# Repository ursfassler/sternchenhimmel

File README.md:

# Sternchenhimmel #

A small starry sky for sweat dreams.

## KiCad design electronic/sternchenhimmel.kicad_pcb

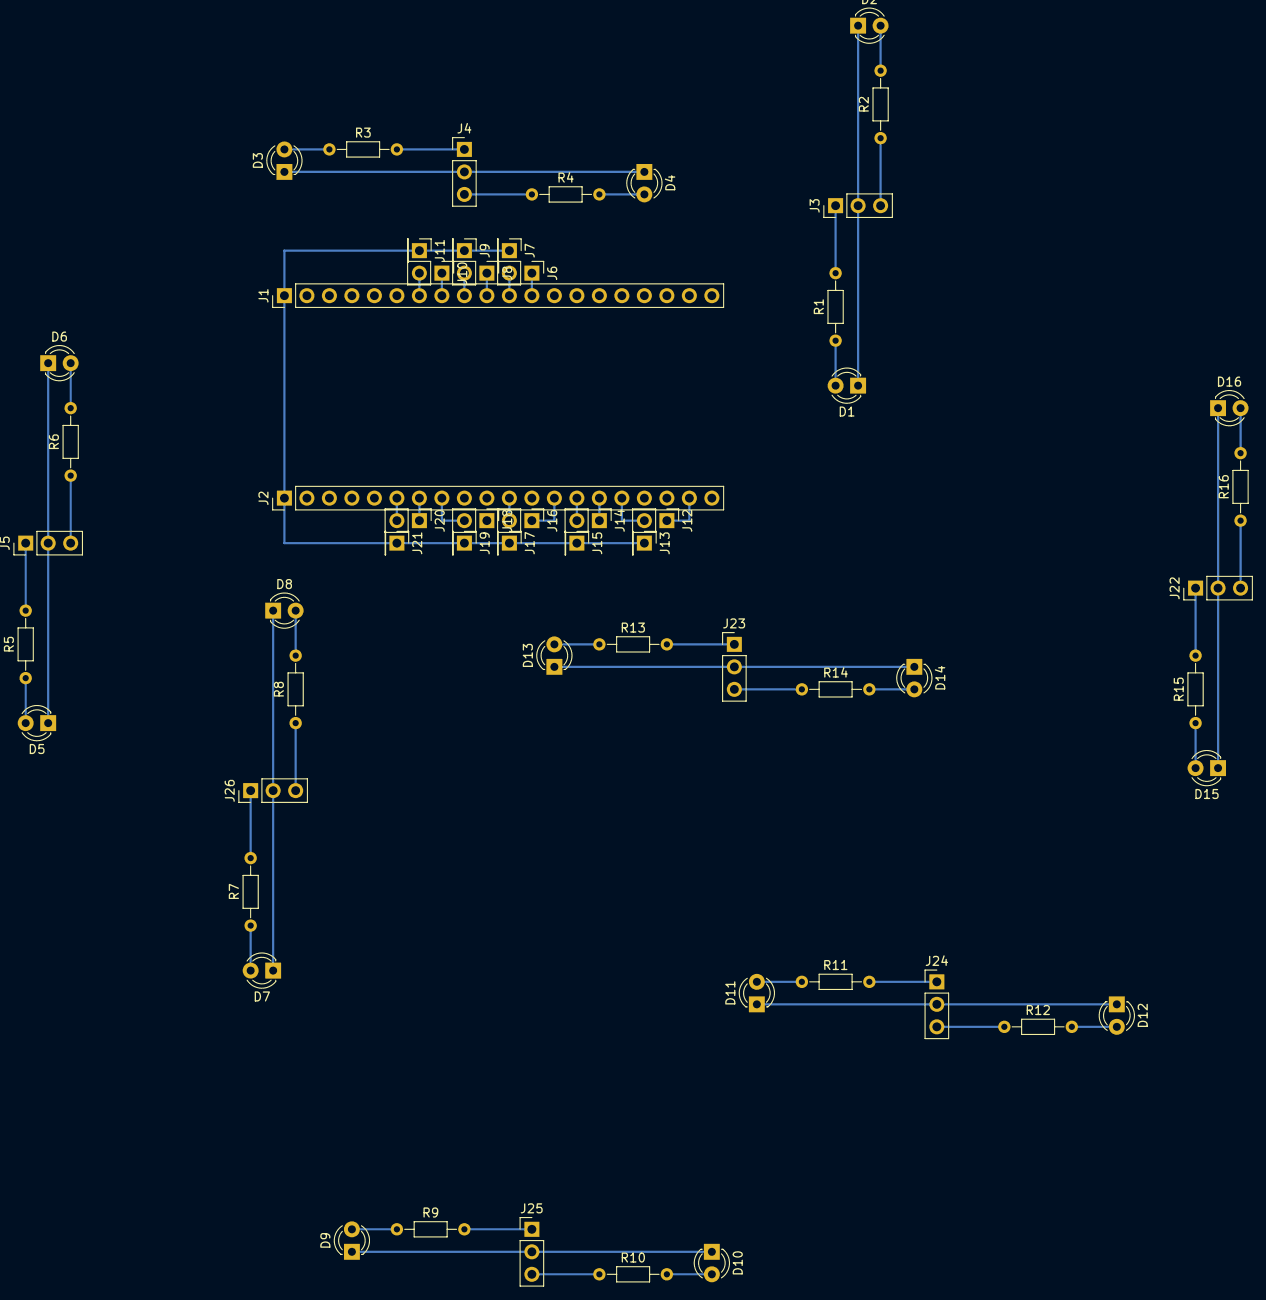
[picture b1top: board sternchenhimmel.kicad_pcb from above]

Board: 2 copper layers, 58 parts (0 on the bottom side), 57 nets.

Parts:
D1, D2, D3, D4, D5, D6, D7, D8, D9, D10, D11, D12, D13, D14, D15, D16: Yellow; LED_D3.0mm
J1, J2: ESP32 Thing; Pin_Header_Straight_1x20_Pitch2.54mm
J3, J4, J5, J22, J23, J24, J25, J26: Conn_01x03; Pin_Header_Straight_1x03_Pitch2.54mm
J6, J8, J10, J12, J14, J16, J18, J20: Conn_01x02; Pin_Header_Straight_1x02_Pitch2.54mm
J7, J9, J11, J13, J15, J17, J19, J21: Conn_01x01; Pin_Header_Straight_1x01_Pitch2.54mm
R1, R2, R3, R4, R5, R6, R7, R8, R9, R10, R11, R12, R13, R14, R15, R16: 470; R_Axial_DIN0204_L3.6mm_D1.6mm_P7.62mm_Horizontal

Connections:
/IO_2: J2.10, J18.1
/IO_4: J2.8, J18.2
/IO_10: J2.13, J16.1
/IO_12: J1.8, J10.1
/IO_13: J1.7, J10.2
/IO_14: J1.9, J8.2
/IO_15: J2.11, J16.2
/IO_16: J2.6, J20.2
/IO_17: J2.7, J20.1
/IO_19: J2.15, J14.1
/IO_21: J2.19, J12.1
/IO_22: J2.16, J12.2
/IO_23: J2.14, J14.2
/IO_25: J1.12, J6.1
/IO_26: J1.11, J6.2
/IO_27: J1.10, J8.1
GND: J1.1, J2.1, J7.1, J9.1, J11.1, J13.1, J15.1, J17.1, J19.1, J21.1
unnamed: D1.1, D2.1, J3.2
unnamed: D1.2, R1.1
unnamed: D2.2, R2.2
unnamed: D3.1, D4.1, J4.2
unnamed: D3.2, R3.1
unnamed: D4.2, R4.2
unnamed: D5.1, D6.1, J5.2
unnamed: D5.2, R5.1
unnamed: D6.2, R6.2
unnamed: D7.1, D8.1, J26.2
unnamed: D7.2, R7.1
unnamed: D8.2, R8.2
unnamed: D9.2, R9.1
unnamed: D9.1, D10.1, J25.2
unnamed: D10.2, R10.2
unnamed: D11.1, D12.1, J24.2
unnamed: D11.2, R11.1
unnamed: D12.2, R12.2
unnamed: D13.1, D14.1, J23.2
unnamed: D13.2, R13.1
unnamed: D14.2, R14.2
unnamed: D15.1, D16.1, J22.2
unnamed: D15.2, R15.1
unnamed: D16.2, R16.2
unnamed: J3.1, R1.2
unnamed: J3.3, R2.1
unnamed: J4.1, R3.2
unnamed: J4.3, R4.1
unnamed: J5.1, R5.2
unnamed: J5.3, R6.1
unnamed: J22.1, R15.2
unnamed: J22.3, R16.1
unnamed: J23.1, R13.2
unnamed: J23.3, R14.1
unnamed: J24.1, R11.2
unnamed: J24.3, R12.1
unnamed: J25.1, R9.2
unnamed: J25.3, R10.1
unnamed: J26.1, R7.2
unnamed: J26.3, R8.1

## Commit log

2018-01-18 add description
2018-01-18 add designs
2018-01-27 add model for 3D printing
2018-01-27 add schematic
2018-01-27 add software
2018-02-02 use C++14
2018-03-25 change layout and schematic for pcb based LED position
2018-04-27 laser cutter model
